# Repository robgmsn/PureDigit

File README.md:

# GMSN! Pure Digit
  
cc-by 4.0

Rob Spencer

[gmsn.co.uk](https://gmsn.co.uk)

[forum.gmsn.co.uk](https://forum.gmsn.co.uk)

Open Source Synth Designs.

DESIGN STATUS: Awaiting Testing - Ready for beta testing

Digit Updated to V2.0 28/4/21

RC filter added to DAC output.
Cap added to output opamp.
SD Card Reader added.

To do: Replace power so 5V comes from case power supply, inline with low noise techniques. May require complete redesign.

### Intro
This repo contains both the Library and Sketches for the GMSN! Pure Digit.

A small programmable utility module which accepts +/- 10V in,
does some digital processing, and outputs a +/-10V signal.

It has a 2 Channel 12bit ADC In, 12bit DAC Out, a 24
position rotary encoder with switch and a 7 segment LED display.

## To install the library

The library is installed via the normal Arduino Library management system.
  
1. From within the Arduino IDE, click on Sketch>Include Library>Manage Libraries...
  
2. Search for "GMSN" and click install.

### Sketches   
- [x] VCO
- [x] Noise
- [x] EmptySketch
- [x] RandomSequencer
- [ ] Clock Divider
- [ ] MicroTuner
- [x] BitCrusher
- [ ] Drums
- [ ] RhythmPlayer
- [ ] SwingMachine
- [ ] LFO
- [ ] StepLFO
- [x] DCLevel
- [ ] Module Testing Functions
- [ ] FrequencyCounter
- [ ] DCMeter

### Methods

encodeVal(int value) - Call this to increment or decrement a value with the rotary encoder.

displayLED(int digit, byte mode, bool dp) - The display has two modes:
                              1) Standard 0 - 9 digital digit.
                              2) Positional representation with 12 values. Where the knob is pointing!
                                 This uses the result of a modulo calculation so the value can be greater
                                 than 12 and it will keep rotating. It can't go less than zero though.

displayOff() - Turns the display off.

dacWrite(int value) - Write a value to the DAC. Yes, it's got a 20V P2P voltage!! :D
           0    =   +10V
           2048 =   0V
           4095 =   -10V

dacWriteCal(int value) - Write a value to the DAC, but using the calibration values. Use this when you need to ensure the output matches the module input, especially when processing audio or pitch CV.

adcRead(byte channel) - Read a 20V P2P from the DAC, channel 1 or 2. Voltages as above.

dontCalibrate() - If you don't actually need to use dacWriteCal(), then call dontCalibrate() before begin().

calibrate() - Some applications need the output to follow the output as closely as possible. If you have an audio signal coming in, you want the output to be the same. Due small differences in components, there will be both Gain Error and Offset Error that needs to be accounted for. This is a very simple routine which runs once everytime the module is flashed. The calibration values are then stored in EEPROM and used whenever dacWriteCal() is called.

getSwitchState() - This method returns the state of the switch, 1 for pressed, 0 for not pressed.

### How to calibrate

If the module hasn't been calibrated, it will run through a self calibration routine. You just need a single patch cable, no other modules or test kit required!

First of all the module will flash "8" a few times, before entering the calibration routine.

1) When it displays "1" patch from the output back into input 1.
2) Long Press the encoder.
3) Patch from output into input 2.
4) Long Press the encoder.

It will then count down to zero and flash. The module is now calibrated.

N.B. The calibration settings are stored in EEPROM, which is overwritten every time the module is flashed, therefor the calibration routing will run everytime the module is flashed.

### Example Sketch
```
// A random sequencer with variable delay

#include <Digit.h>                    //Include the Digit library

Digit digit;                          //Create a Digit called digit. This object now has the methods above available to it.

//Setup variables
int encPos = 1;                       //Just some variables for us to use in the code

void setup() {
 digit.begin();                       //Tell digit to configure its self.
}

void loop() {
   encPos = digit.encodeVal(encPos);  //Increment or decrement the varible encPos
   digit.displayLED(encPos, 2, 0);    //Display the value of encPos as a Positional Representation with no decimal point
   digit.dacWrite(random(4095));      //Output a random value between 0 and 4095, which is analogue +/- 10V
   delay(encPos);                     //Delay for encPos milliseconds.
}
```

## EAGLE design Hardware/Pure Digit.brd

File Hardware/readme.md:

DESIGN STATUS: Awaiting Testing - Ready for beta testing

Digit Updated to V1.1 25/4/21

RC filter added to DAC output.
Cap added to output opamp.

To do: Replace power so 5V comes from case power supply, inline with low noise techniques. May require complete redesign.
To do: Read from SD Card.

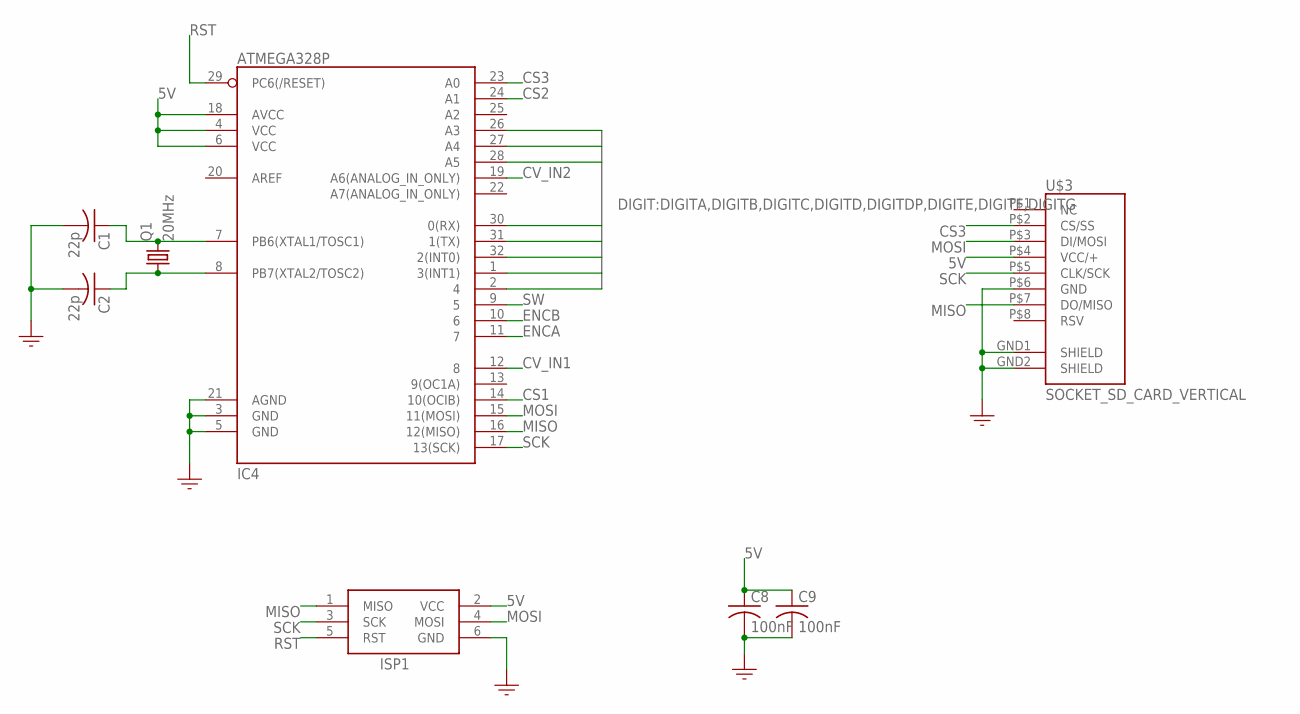
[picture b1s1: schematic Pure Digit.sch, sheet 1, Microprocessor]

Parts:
C1, C2: 22p; C0805
C8, C9: 100nF; C0805
IC4: ATMEGA328P; TQFP32-08
ISP1: HEADER2X3-6; AVRISP
Q1: 20MHz; SM49
U$3: SOCKET_SD_CARD_VERTICAL; PJS008U-3000

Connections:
5V: C8.1, C9.1, IC4.4 (VCC), IC4.6 (VCC), IC4.18 (AVCC), ISP1.2 (VCC), U$3.P$4 (VCC/+); also elsewhere on the board
CS1: IC4.14 (10(OCIB)); also elsewhere on the board
CS2: IC4.24 (A1); also elsewhere on the board
CS3: IC4.23 (A0), U$3.P$2 (CS/SS)
CV_IN1: IC4.12 (8); also elsewhere on the board
CV_IN2: IC4.19 (A6(ANALOG_IN_ONLY)); also elsewhere on the board
DIGITA: IC4.30 (0(RX)); also elsewhere on the board
DIGITB: IC4.28 (A5); also elsewhere on the board
DIGITC: IC4.27 (A4); also elsewhere on the board
DIGITD: IC4.26 (A3); also elsewhere on the board
DIGITDP: IC4.1 (3(INT1)); also elsewhere on the board
DIGITE: IC4.2 (4); also elsewhere on the board
DIGITF: IC4.32 (2(INT0)); also elsewhere on the board
DIGITG: IC4.31 (1(TX)); also elsewhere on the board
ENCA: IC4.11 (7); also elsewhere on the board
ENCB: IC4.10 (6); also elsewhere on the board
GND: C1.2, C2.2, C8.2, C9.2, IC4.3 (GND), IC4.5 (GND), IC4.21 (AGND), ISP1.6 (GND), U$3.GND1 (SHIELD), U$3.GND2 (SHIELD), U$3.P$6 (GND); also elsewhere on the board
MISO: IC4.16 (12(MISO)), ISP1.1 (MISO), U$3.P$7 (DO/MISO); also elsewhere on the board
MOSI: IC4.15 (11(MOSI)), ISP1.4 (MOSI), U$3.P$3 (DI/MOSI); also elsewhere on the board
unnamed: C1.1, IC4.7 (PB6(XTAL1/TOSC1)), Q1.2
unnamed: C2.1, IC4.8 (PB7(XTAL2/TOSC2)), Q1.1
RST: IC4.29 (PC6(/RESET)), ISP1.5 (RST)
SCK: IC4.17 (13(SCK)), ISP1.3 (SCK), U$3.P$5 (CLK/SCK); also elsewhere on the board
SW: IC4.9 (5); also elsewhere on the board

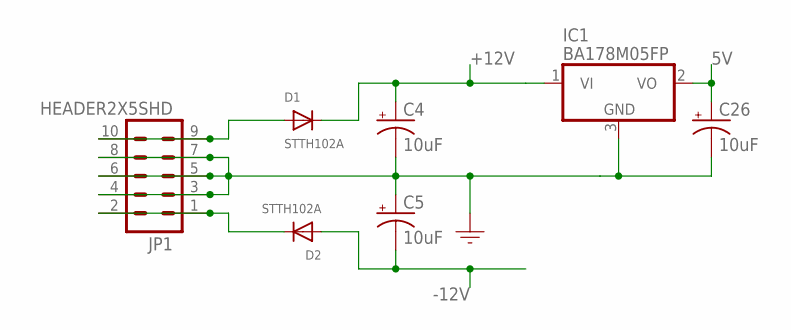
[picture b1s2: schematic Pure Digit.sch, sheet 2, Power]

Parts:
C4, C5, C26: 10uF; 153CLV-0505
D1, D2: STTH102A; SMADIODE
IC1: BA178M05FP; TO252
JP1: HEADER2X5SHD; 2X5-SHROUDED

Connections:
5V: C26.+, IC1.2 (VO); also elsewhere on the board
+12V: C4.+, D1.C, IC1.1 (VI); also elsewhere on the board
-12V: C5.-, D2.A; also elsewhere on the board
GND: C4.-, C5.+, C26.-, IC1.3 (GND), JP1.3, JP1.4, JP1.5, JP1.6, JP1.7, JP1.8; also elsewhere on the board
unnamed: D1.A, JP1.9, JP1.10
unnamed: D2.C, JP1.1, JP1.2

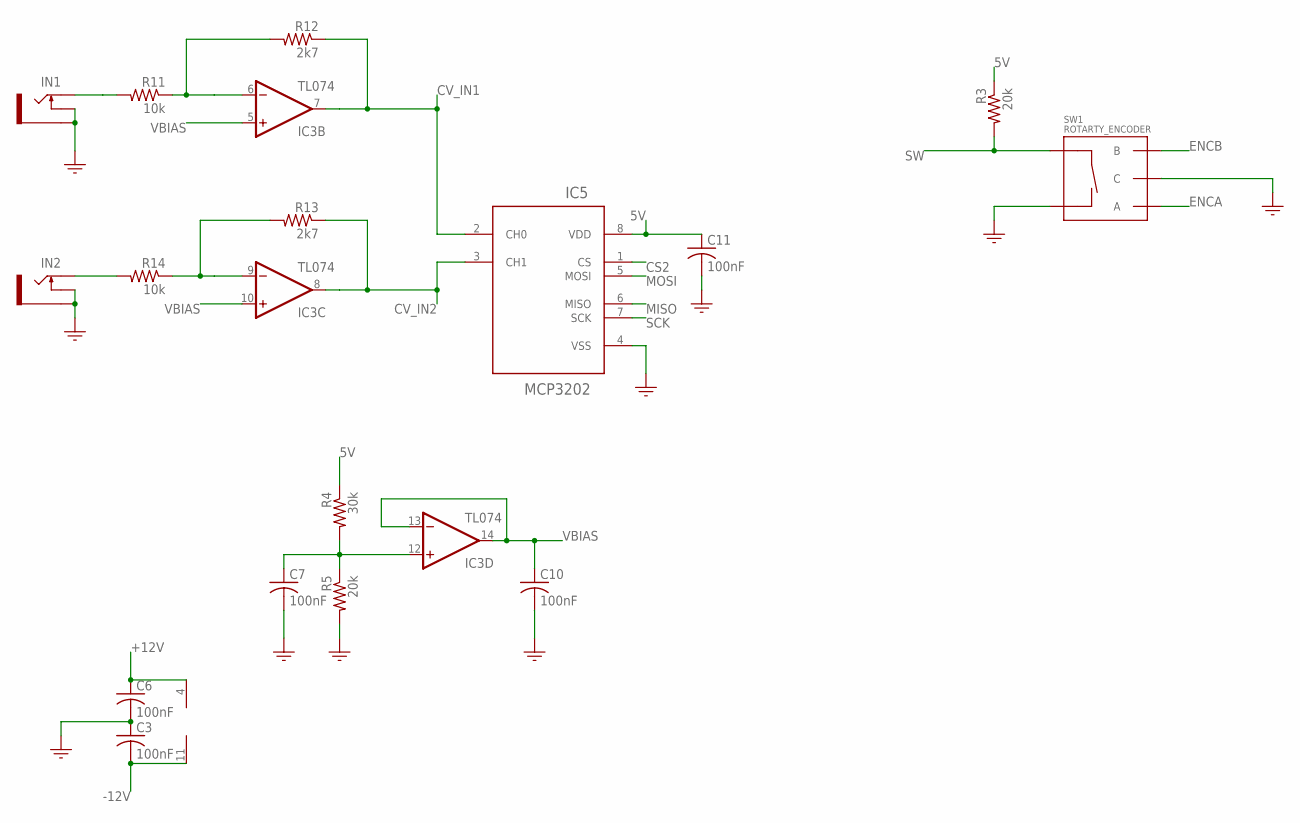
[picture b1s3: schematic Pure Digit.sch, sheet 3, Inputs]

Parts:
C3, C6, C7, C10, C11: 100nF; C0805
IC3: TL074; SO14
IC5: MCP3202; SOIC--8
IN1, IN2: PJ301M-12
R3, R5: 20k; R0805
R4: 30k; R0805
R11, R14: 10k; R0805
R12, R13: 2k7; R0805
SW1: ROTARTY_ENCODER; ROTARY_ENC_PLAIN

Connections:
5V: C11.1, IC5.8 (VDD), R3.1, R4.1; also elsewhere on the board
+12V: C6.1, IC3.4 (V+); also elsewhere on the board
-12V: C3.2, IC3.11 (V-); also elsewhere on the board
CS2: IC5.1 (CS); also elsewhere on the board
CV_IN1: IC3.7 (OUT), IC5.2 (CH0), R12.1; also elsewhere on the board
CV_IN2: IC3.8 (OUT), IC5.3 (CH1), R13.1; also elsewhere on the board
ENCA: SW1.A; also elsewhere on the board
ENCB: SW1.B; also elsewhere on the board
GND: C3.1, C6.2, C7.2, C10.2, C11.2, IC5.4 (VSS), IN1.GND (SLEEVE), IN1.NORM (SWITCH), IN2.GND (SLEEVE), IN2.NORM (SWITCH), R5.2, SW1.C, SW1.SW-; also elsewhere on the board
MISO: IC5.6 (MISO); also elsewhere on the board
MOSI: IC5.5 (MOSI); also elsewhere on the board
unnamed: IN1.TIP, R11.2
unnamed: IN2.TIP, R14.2
unnamed: C7.1, IC3.12 (+IN), R4.2, R5.1
unnamed: IC3.6 (-IN), R11.1, R12.2
unnamed: IC3.9 (-IN), R13.2, R14.1
SCK: IC5.7 (SCK); also elsewhere on the board
SW: R3.2, SW1.SW+; also elsewhere on the board
VBIAS: C10.1, IC3.5 (+IN), IC3.10 (+IN), IC3.13 (-IN), IC3.14 (OUT)

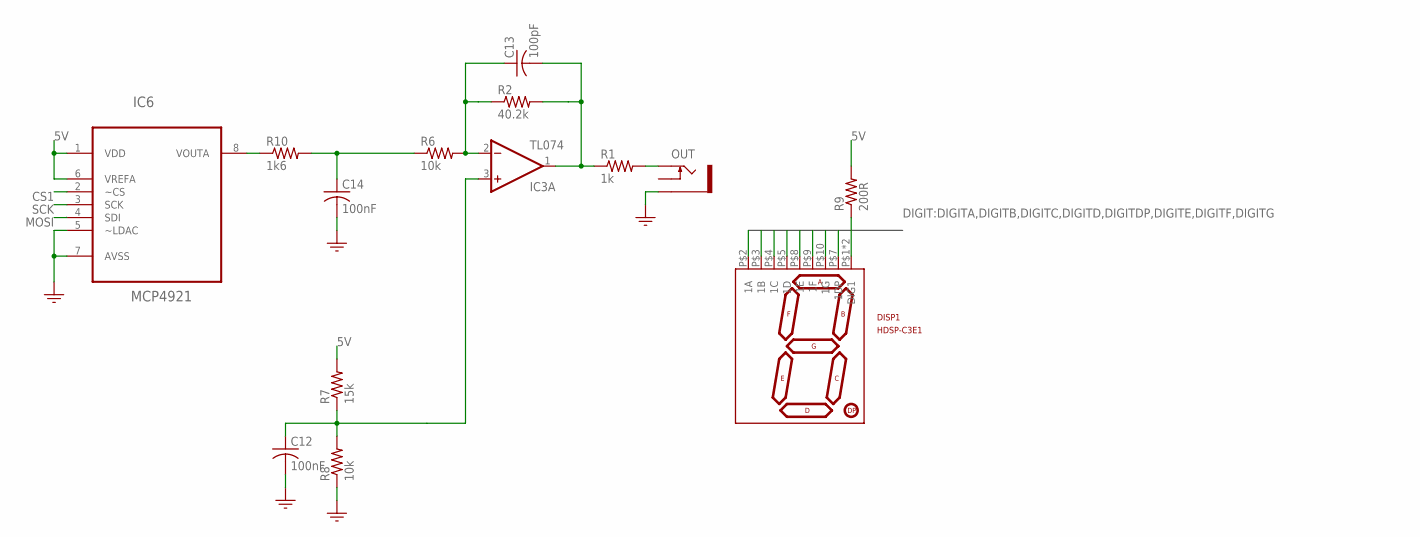
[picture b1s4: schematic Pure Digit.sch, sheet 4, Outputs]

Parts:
C12, C14: 100nF; C0805
C13: 100pF; C0805
DISP1: HDSP-C3E1; 7-SEGMENT-1DIGIT
IC3: TL074; SO14
IC6: MCP4921; SOIC8
OUT: PJ301M-12
R1: 1k; R0805
R2: 40.2k; R0805
R6, R8: 10k; R0805
R7: 15k; R0805
R9: 200R; R0805
R10: 1k6; R0805

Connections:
5V: IC6.1 (VDD), IC6.6 (VREFA), R7.2, R9.2; also elsewhere on the board
CS1: IC6.2 (~CS); also elsewhere on the board
DIGITA: DISP1.P$2 (1A); also elsewhere on the board
DIGITB: DISP1.P$3 (1B); also elsewhere on the board
DIGITC: DISP1.P$4 (1C); also elsewhere on the board
DIGITD: DISP1.P$5 (1D); also elsewhere on the board
DIGITDP: DISP1.P$7 (1DP); also elsewhere on the board
DIGITE: DISP1.P$8 (1E); also elsewhere on the board
DIGITF: DISP1.P$9 (1F); also elsewhere on the board
DIGITG: DISP1.P$10 (1G); also elsewhere on the board
GND: C12.2, C14.2, IC6.5 (~LDAC), IC6.7 (AVSS), OUT.GND (SLEEVE), R8.1; also elsewhere on the board
MOSI: IC6.4 (SDI); also elsewhere on the board
unnamed: C12.1, IC3.3 (+IN), R7.1, R8.2
unnamed: C13.2, IC3.1 (OUT), R1.1, R2.2
unnamed: OUT.TIP, R1.2
unnamed: C14.1, R6.1, R10.2
unnamed: C13.1, IC3.2 (-IN), R2.1, R6.2
unnamed: DISP1.P$1 (DIG1), DISP1.P$6 (DIG1), R9.1
unnamed: IC6.8 (VOUTA), R10.1
SCK: IC6.3 (SCK); also elsewhere on the board

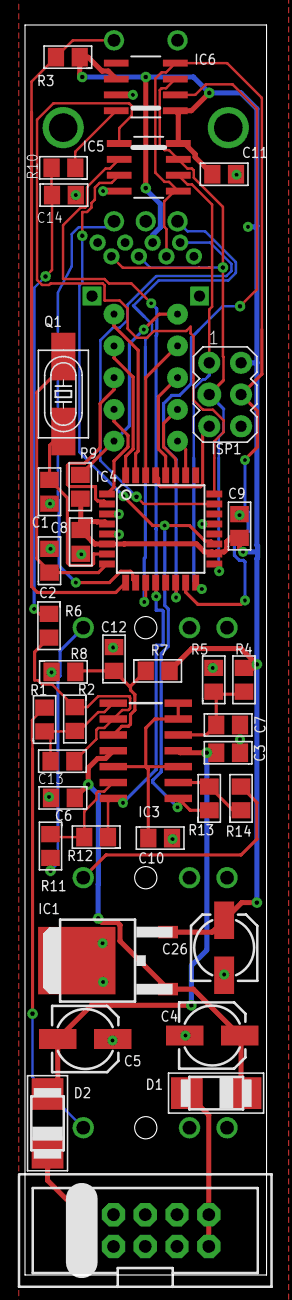
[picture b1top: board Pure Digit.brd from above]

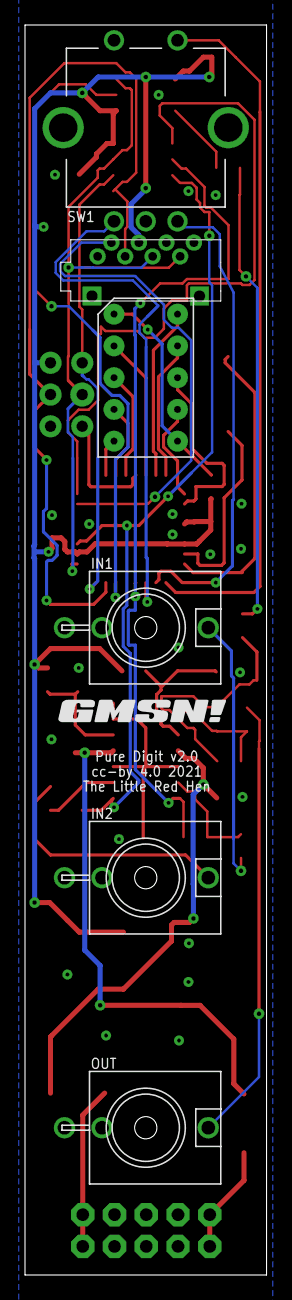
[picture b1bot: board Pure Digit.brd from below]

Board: 2 copper layers, 19.3 x 100.0 mm, 46 parts (7 on the bottom side), 41 nets.

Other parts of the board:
U$1: GMSN!_LOGO

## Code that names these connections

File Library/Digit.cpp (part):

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#include "Digit.h"

//Setup Digit
#define digitA 0 //30
#define digitB A5 //28
#define digitC A4 //27
#define digitD A3 //26
#define digitE 4 //2
#define digitF 2 //32
#define digitG 1 //31
#define digitDP 3 //1

//Setup Encoder
  //SW
#define sw 5 //9

  //Encoder
#define encA 7 //11
#define encB 6 //10


//Setup SPI Bus
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void Digit::begin() {

  //Setup Digit Pins
  pinMode(digitA, OUTPUT);
  pinMode(digitB, OUTPUT);
  pinMode(digitC, OUTPUT);
  pinMode(digitD, OUTPUT);
  pinMode(digitE, OUTPUT);
  pinMode(digitF, OUTPUT);
  pinMode(digitG, OUTPUT);
  pinMode(digitDP, OUTPUT);

  digitalWrite(digitA, HIGH);
  digitalWrite(digitB, HIGH);
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
  //Setup Encoder Pins
  pinMode(sw, INPUT);
  pinMode(encA, INPUT);
  pinMode(encB, INPUT);
  digitalWrite(encA, HIGH);
  digitalWrite(encB, HIGH);

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
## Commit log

2018-08-07 Library Added
2018-08-07 Initial Readme
2018-08-07 Rename Library/library.properties to library.properties
2018-08-07 Rename examples/noise.ino to examples/Noise/Noise.ino
2018-08-07 Rename examples/Noise/Noise.ino to examples/RandomSequencer/RandomSequencer.ino
2018-08-07 DC Level Added to examples
2018-08-07 Updated EmptySketch
2018-08-15 Self Calibration added
2018-08-15 Additional methods added
2018-09-04 added Don't Calibrate methods
2018-09-05 adding LFO example
2018-09-07 First release
2018-09-07 fixed rate multiplier
2018-09-07 removed some comments
2018-09-28 Pre Inter / sections update
2018-09-28 More Pre Inter /sections updates.
2018-10-07 Enc 9 now goes twice as slow
2018-10-07 Added Readme
2018-10-08 Added support for digits 10-19 and encoder loop at <0 and >19
2018-10-14 Added displayRandom() to digit library
2018-10-14 Added Predator Mode to the LFO to indicate the frequency of the LFO
2018-10-31 Updated Install instructions
    Library now available via the Arduino Library management system
2018-11-01 Added support for characters -, M, m, C, P, b, H
2021-04-25 Digit 1.1
    Digit Updated to V1.1 25/4/21
    RC filter added to DAC output.
    Cap added to output opamp.
    To do: Replace power so 5V comes from case power supply, inline with low noise techniques. May require complete redesign.
    To do: Read from SD Card.
2021-04-28 Digit 2.0
    Digit Updated to V2.0 28/4/21
    RC filter added to DAC output.
    Cap added to output opamp.
    SD Card Reader added.
    To do: Replace power so 5V comes from case power supply, inline with low noise techniques. May require complete redesign.

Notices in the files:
Hardware/Pure Digit.brd:
cc-by 4.0 2021
